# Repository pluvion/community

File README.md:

# Pluvi.On – Hackeando a chuva (Hacking the rain)

Hoje no Brasil, existem aproximadamente 30 milhões de brasileiros expostos ao risco de enchentes e inundações. Além disso, existe uma projeção de impacto financeiro, onde as potenciais perdas anuais podem chegar a 4 bilhões de dólares até 2030 (Fonte: Swiss Re)

_Today in Brazil, there are approximately 30 million Brazilians exposed to the risk of flash floods and river floods. Moreover, there is financial impact: potential annual losses can reach 4 billion dollars by 2030 (Source: Swiss Re)_

Olhando este cenário alarmante iniciamos o desenvolvimento do Pluvi.On em jun/2016. Hoje somos um serviço de medição de chuva em tempo real e hiperlocalmente que envia informações de volume e intensidade da precipitação para quem precisar, população, entes governamentais e empresas.

_Looking at this alarming scenario we started the development of Pluvi.On in jun / 2016. Today we are a real-time and hyperlocal rainfall service that sends accumulated volume and precipitation rate data to anyone who needs it, population, government entities and companies._

Nosso sonho grande consiste em desenvolver novas estratégias de alerta de riscos (inundações, deslizamentos e chuvas intensas) para toda a população. Se possível, de maneira barata e escalável para que esta informação chegue a quem realmente precisa.

_Our big dream is to develop new risk alert strategies (floods, landslides and heavy rains) for the entire population. If possible, cheaply and scalable enough that this information gets to who really needs it._

Uma parte importante de tudo isso é o Pluvi.On, uma estação meteorológica Open Source e de baixo custo para ser espalhada na maior quantidade de pontos da cidade que pudermos!!! Chega de blá blá blá e vamos ao que interessa:

_An important part of all this is Pluvi.On itself, an inexpensive Open Source weather station to be spread out in as many points of the city as we can !!! That&#39;s enough talk let&#39;s see what matters:_

Você pode checar neste link todas as instruções para construção do seu próprio Pluvi!

_You can check in this link all the instructions for building your own Pluvi!_

https://www.instructables.com/member/PluviOn/

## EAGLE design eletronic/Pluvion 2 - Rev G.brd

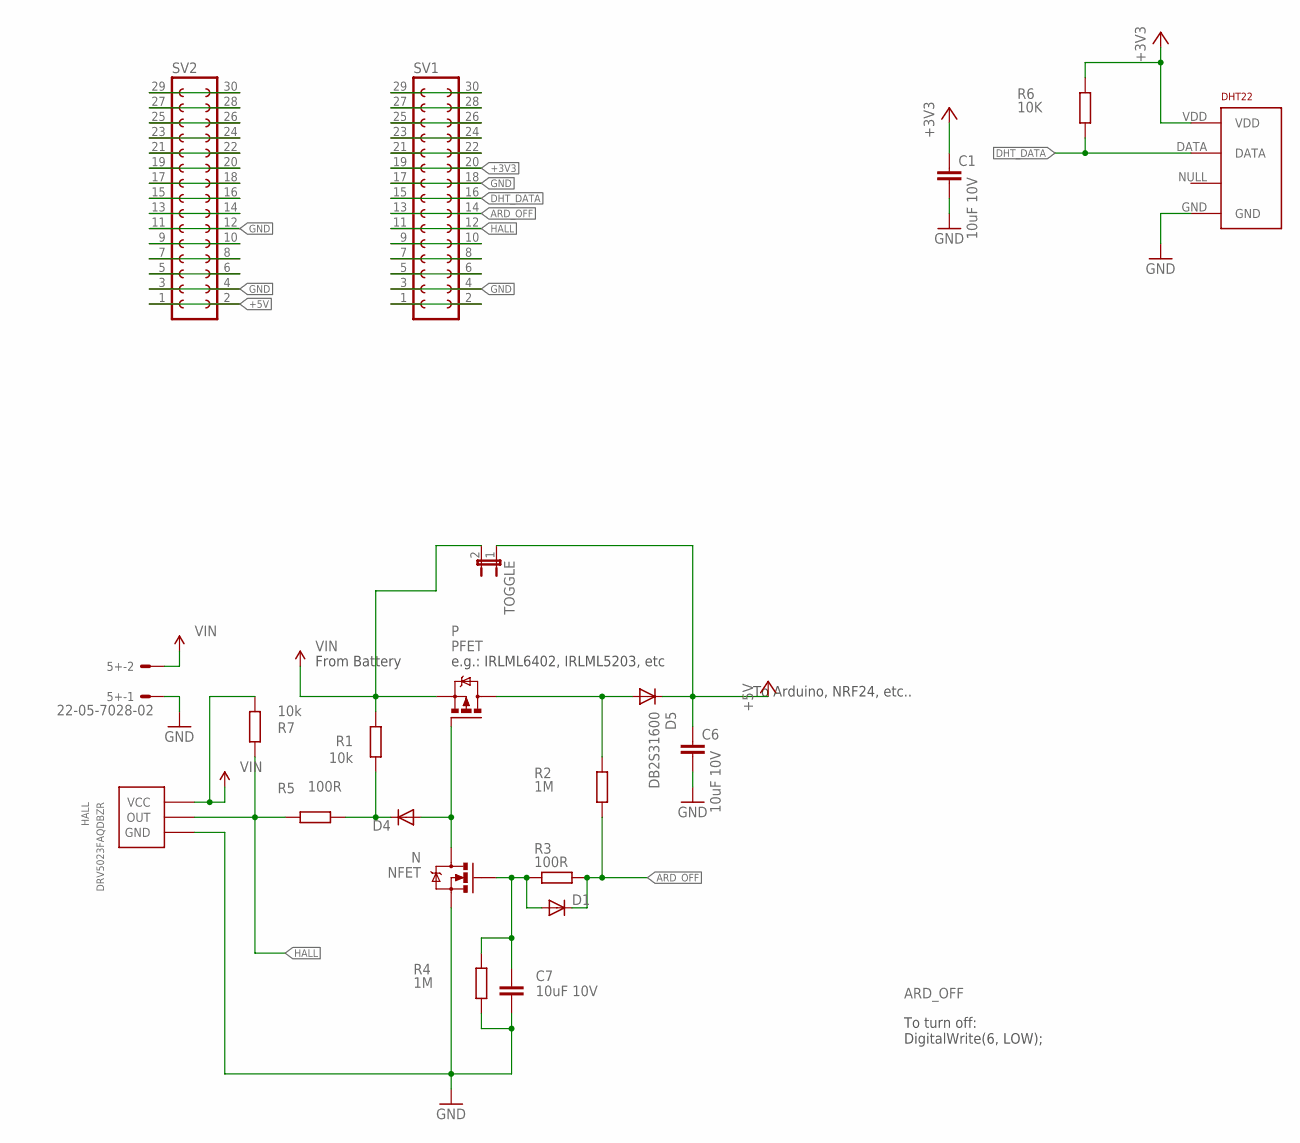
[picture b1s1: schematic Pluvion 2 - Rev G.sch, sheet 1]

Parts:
5+: 22-05-7028-02; 7395-02
C1, C6, C7: 10uF 10V; C0805
D1, D4: DIODESOD; SOD-323
D5: DB2S31600; SMA-DIODE
DHT22: RHT03_DHT-22_AM2302RA; RHT03_DHT-22/RA
HALL: DRV5023FAQDBZR; SOT23
N: NFET; SOT23
P: PFET; MICRO3
R1, R7: 10k; R0805
R2, R4: 1M; R0805
R3, R5: 100R; R0805
R6: 10K; R0805
SV1, SV2: FE15-2
TOGGLE: JUMPER-2PTH; 1X02

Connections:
+3V3: C1.1, DHT22.VDD, R6.2, SV1.19, SV1.20
+5V: C6.1, D5.C, SV2.1, SV2.2, TOGGLE.1
ARD_OFF: D1.1 (C), R2.1, R3.2, SV1.13, SV1.14
BUTTONS: D4.2 (A), N.3 (D), P.1 (G)
DHT_DATA: DHT22.DATA, R6.1, SV1.15, SV1.16
GND: 5+.1, C1.2, C6.2, C7.2, DHT22.GND, HALL.3 (GND), N.2 (S), R4.1, SV1.3, SV1.4, SV1.17, SV1.18, SV2.3, SV2.4, SV2.11, SV2.12
HALL: HALL.2 (OUT), R5.2, R7.2, SV1.11, SV1.12
unnamed: D5.A, P.3 (D), R2.2
unnamed: C7.1, D1.2 (A), N.1 (G), R3.1, R4.2
unnamed: SV1.1, SV1.2
unnamed: SV1.5, SV1.6
unnamed: SV1.7, SV1.8
unnamed: SV1.9, SV1.10
unnamed: D4.1 (C), R1.1, R5.1
unnamed: SV1.21, SV1.22
unnamed: SV1.23, SV1.24
unnamed: SV1.25, SV1.26
unnamed: SV1.27, SV1.28
unnamed: SV1.29, SV1.30
unnamed: SV2.5, SV2.6
unnamed: SV2.7, SV2.8
unnamed: SV2.9, SV2.10
unnamed: SV2.13, SV2.14
unnamed: SV2.15, SV2.16
unnamed: SV2.17, SV2.18
unnamed: SV2.19, SV2.20
unnamed: SV2.21, SV2.22
unnamed: SV2.23, SV2.24
unnamed: SV2.25, SV2.26
unnamed: SV2.27, SV2.28
unnamed: SV2.29, SV2.30
VIN: 5+.2, HALL.1 (VCC), P.2 (S), R1.2, R7.1, TOGGLE.2

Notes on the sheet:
e.g.: IRLML6402, IRLML5203, etc
To Arduino, NRF24, etc..
To turn off: DigitalWrite(6, LOW);
From Battery

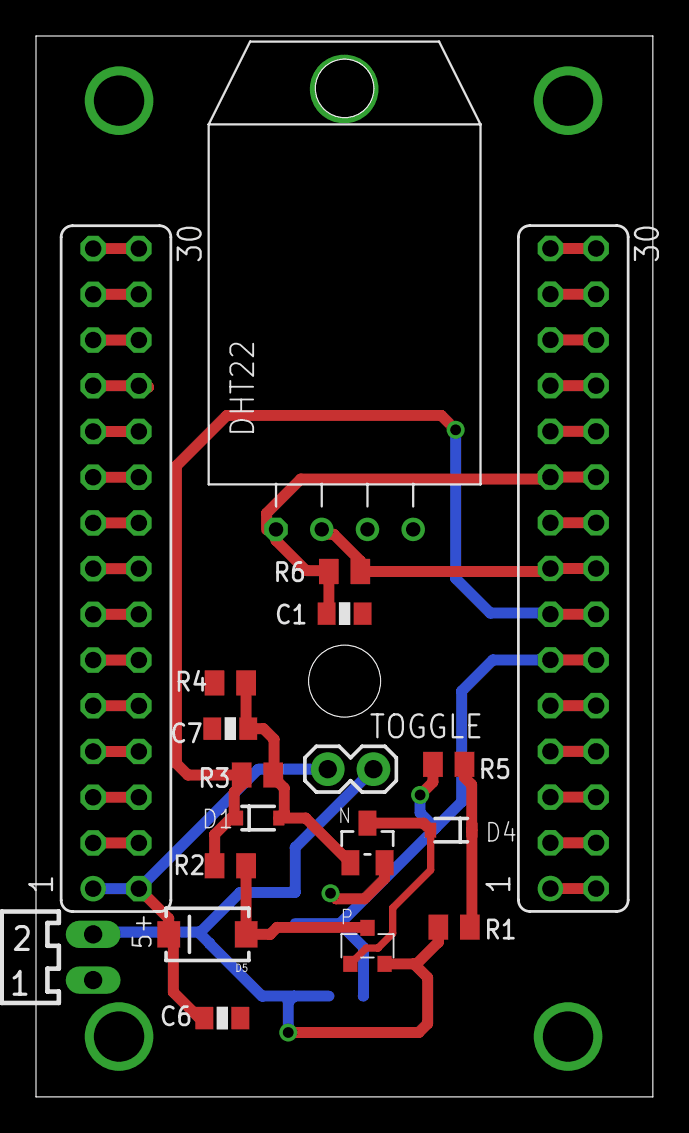
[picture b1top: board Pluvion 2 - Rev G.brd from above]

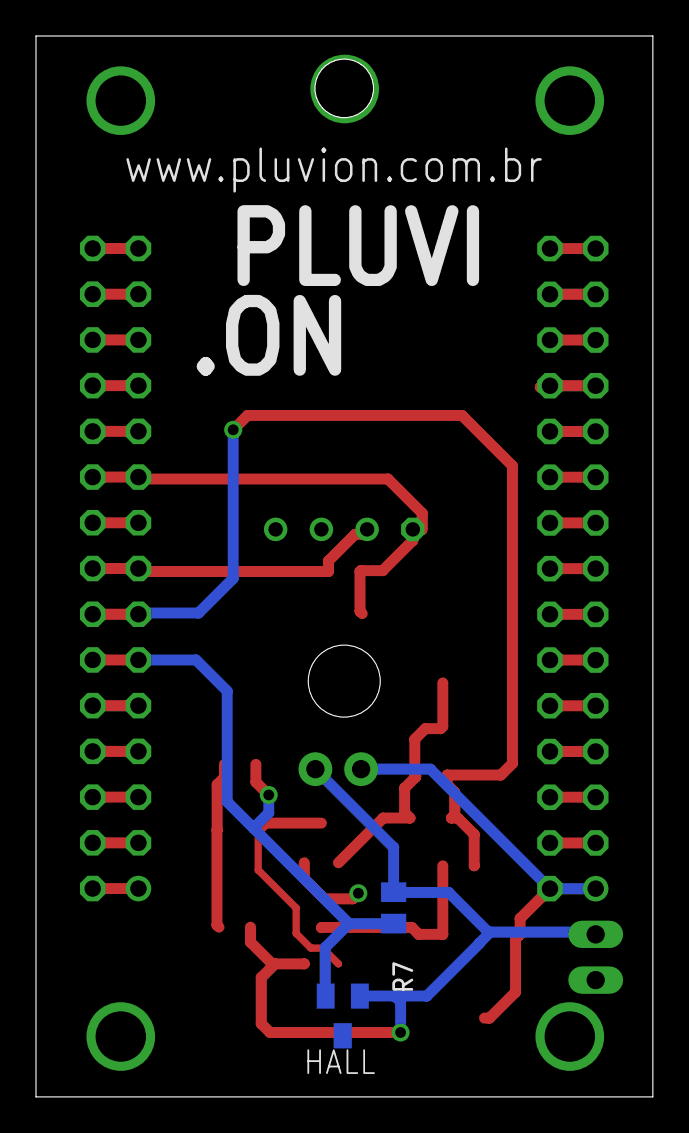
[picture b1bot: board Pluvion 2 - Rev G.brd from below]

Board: 2 copper layers, 34.3 x 58.9 mm, 21 parts (2 on the bottom side), 32 nets.

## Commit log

2017-07-14 updates BOM
2017-07-14 MD update
2017-07-14 updates MD
2017-08-26 New Community API. Fixes in WiFiManager libraries
2017-09-11 OSX Sierra Driver
2017-09-12 Adding sketch folder
2018-01-18 Fixing SSL Certificate error
2019-08-20 add thingspeak fw version
2020-03-11 removing community firmware

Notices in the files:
parts and their libraries:
SparkFun-DiscreteSemi: Licensing: CC v3.0 Share-Alike You are welcome to use this library for commercial purposes.
